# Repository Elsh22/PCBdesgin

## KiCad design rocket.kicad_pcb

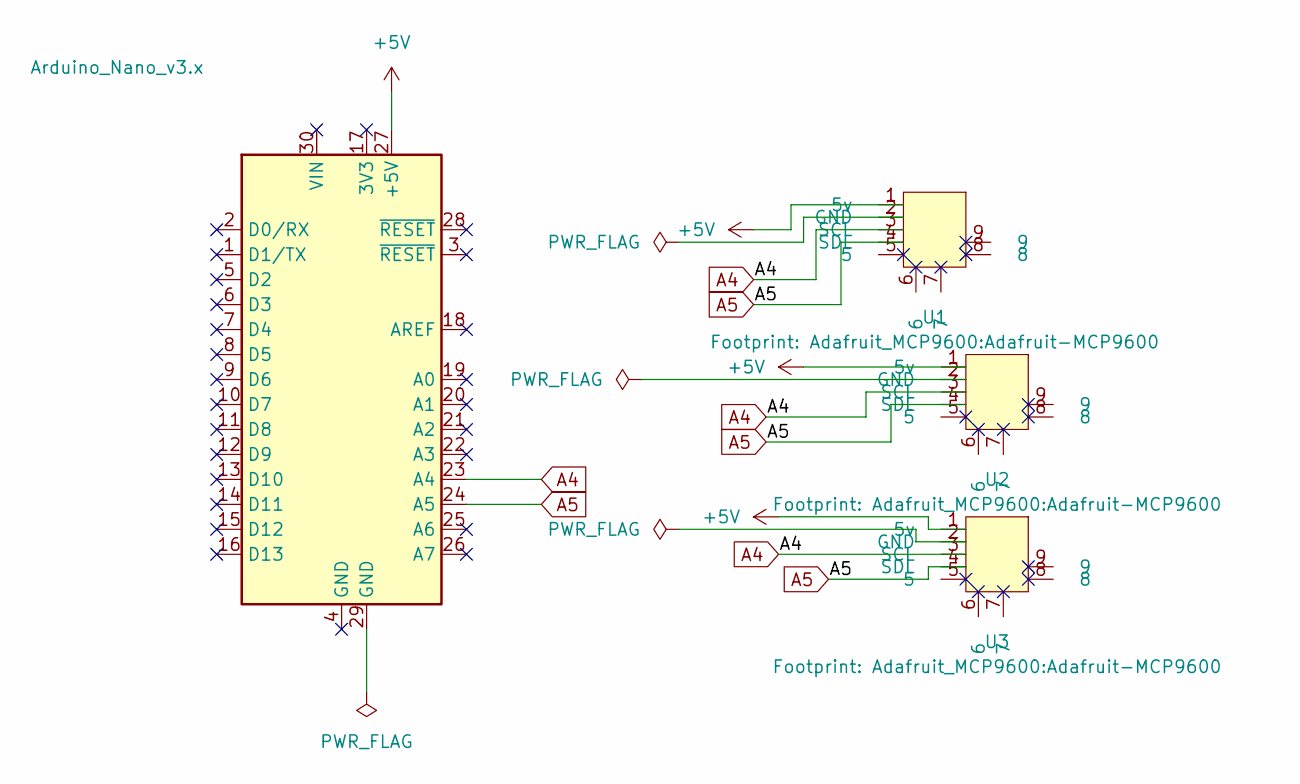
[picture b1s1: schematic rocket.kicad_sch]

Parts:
A1: Arduino_Nano_v3.x; Arduino_Nano
U1, U2, U3: Adafruit-MCP9600

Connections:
+5V: A1.27 (+5V), U1.1 (5v), U2.1 (5v), U3.1 (5v)
A4: A1.23 (A4), U1.3 (SCL), U2.3 (SCL), U3.3 (SCL)
A5: A1.24 (A5), U1.4 (SDL), U2.4 (SDL), U3.4 (SDL)
unnamed: A1.29 (GND), U1.2 (GND), U2.2 (GND), U3.2 (GND)

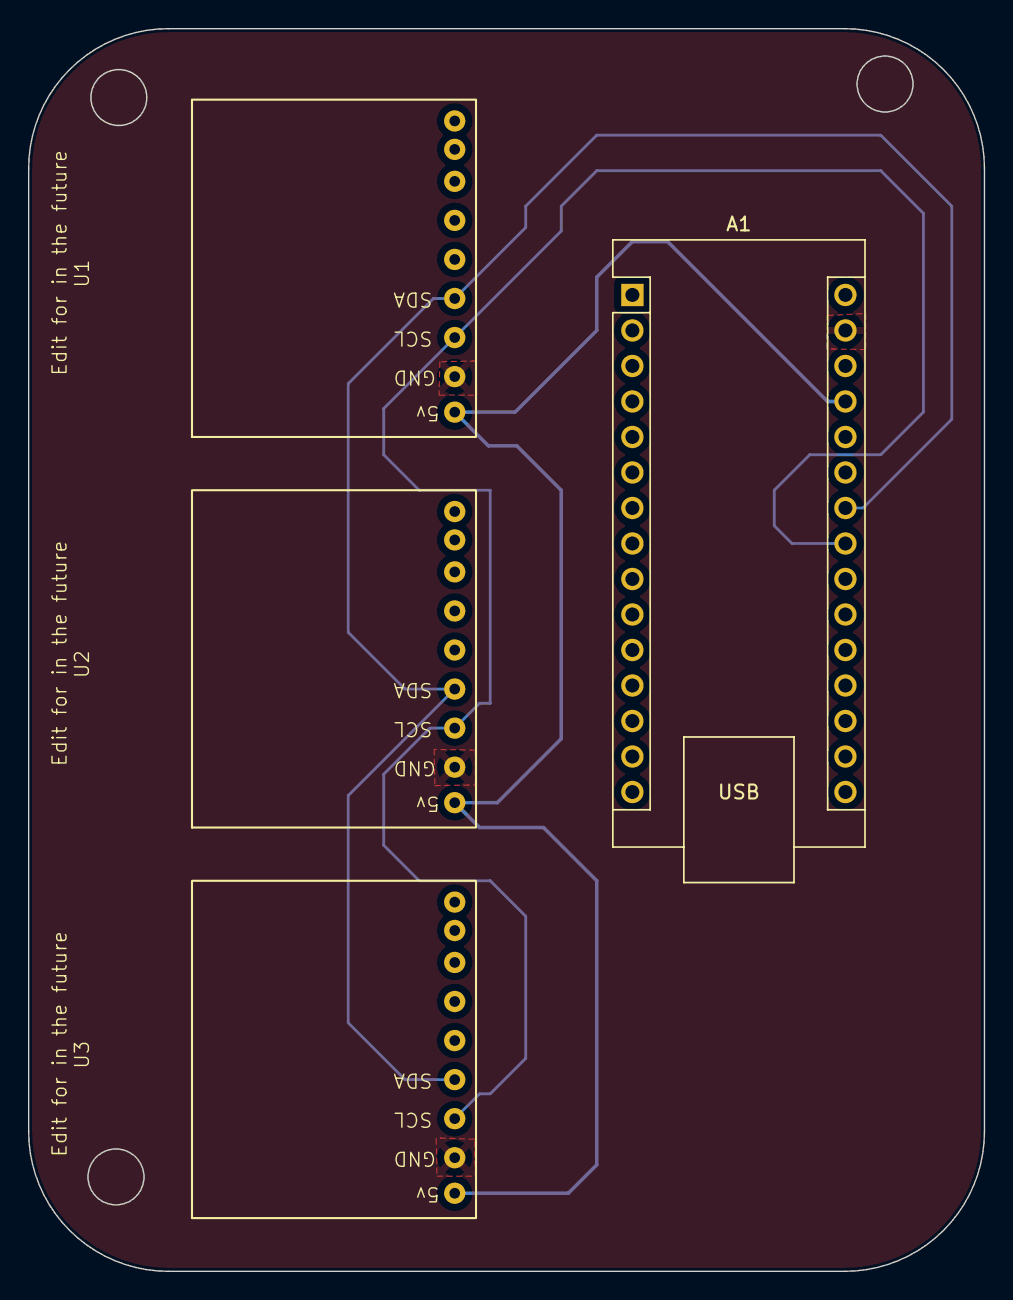
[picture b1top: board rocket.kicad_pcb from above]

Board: 2 copper layers, 68.4 x 88.9 mm, 4 parts (0 on the bottom side), 4 nets.

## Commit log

2024-02-21 Kicad desgin for themrocouples
2024-02-21 PCB Desgin
